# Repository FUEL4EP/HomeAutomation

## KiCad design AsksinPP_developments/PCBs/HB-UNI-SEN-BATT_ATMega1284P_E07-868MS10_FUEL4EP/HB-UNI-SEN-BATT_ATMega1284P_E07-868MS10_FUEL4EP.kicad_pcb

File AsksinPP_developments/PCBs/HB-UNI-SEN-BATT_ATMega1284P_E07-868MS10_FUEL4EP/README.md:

# HB-UNI-SEN-BATT_ATMega1284P_E07-868MS10_FUEL4EP  

**Platine für DIY AsksinPP für**
- eingebauter SMD TQFP-44 [ATMega1284P](https://ww1.microchip.com/downloads/en/DeviceDoc/doc8059.pdf) mit 128kByte Programmspeicher, 16kByte SRAM, 4kByte EEPROM
- [eByte E07-868MS10 Sendemodul](https://www.rcscomponents.kiev.ua/datasheets/e07-868ms10_usermanual_en_v1_20.pdf)
- Bestückungsoption für [Waveshare ePaper Modul (1.54inch (B)](https://www.waveshare.com/product/1.54inch-e-paper-module.htm)
- Bestückungsoption für [TPS61221 Aufwärtswandler](https://www.ti.com/lit/ds/symlink/tps61221.pdf?ts=1634546965861&ref_url=https%253A%252F%252Fwww.ti.com%252Fproduct%252FTPS61221) bei NiMH Akkumulatorbetrieb
- alle SMD Bausteine sind mit dem JLCPCB SMT Bestückungsservice kostengünstig und qualitativ hochwertig bestückbar, das ist also auch für Grobmotoriker wie mich geeignet :-)
- die Bestückungsoption ePaper wurde noch nicht validiert!

## Hinweis

- da das Funkmodul eByte E07-868MS10 (fast) nicht mehr  käuflich zu erhalten ist, wurde die Platine [HB-UNI-SEN-BATT_ATMega1284P_E07-900MM10S_FUEL4EP](https://github.com/FUEL4EP/HomeAutomation/tree/master/AsksinPP_developments/PCBs/HB-UNI-SEN-BATT_ATMega1284P_E07-900MM10S_FUEL4EP) basierend auf dem gut erhältlichen Funkmodul eByte E07-900MM10S entwickelt.

## Credits

- diese Platine ist von Alexander Reinerts Platine [HB-UNI-SEN-BATT](https://github.com/alexreinert/PCB/tree/master/HB-UNI-SEN-BATT) abgeleitet.
- vielen Dank an Alexander Reinert für die Vorarbeit.

## Platine wurde nach Fertigung bei JLCPCB erfolgreich validiert

- entwickelt mit KiCAD 6.0.11
- die Platine wurde bei JLCPCB gefertigt und mit den SMD Bauteilen bestückt
; die nicht SMD Bauteile müssen von Hand verlötet werden
- die gefertigte Platine wurde erfolgreich **ohne** Aufwärtswandler mit dem Sketch [HB-UNI-SENSOR1-AQ-BME680_KF](https://github.com/FUEL4EP/HomeAutomation/tree/master/AsksinPP_developments/sketches/HB-UNI-Sensor1-AQ-BME680_KF) validiert:

- **Update 21. Aug 2023:** Die gefertigte Platine wurde erfolgreich **mit** dem Aufwärtswandler TPS61221 validiert:

	+ die Platine wurde bei JLCPCB gefertigt und einschließlich der Induktivität mit den SMD Bauteilen bestückt 
	+ im Bild wurde ein AA-Akkumulator wurde durch eine AA-Dummy- Batterie ersetzt
	+ Betrieb ist mit einer oder zwei AA Akkumulatorbatterien möglich
	+ die Ausgangsspannung des Aufwärtswandlers beträgt 3.3 Volt
	+ der Jumper JP2 ist bei Betrieb mit einem Aufwärtswandler zu durchtrennen
	+ der Jumper JP3 ist ist bei Betrieb mit einem Aufwärtswandler mit einer Lötbrücke zu versehen

## Eigenschaften

- abgeleitet aus [HB-UNI-SEN-BATT](https://github.com/alexreinert/PCB/tree/master/HB-UNI-SEN-BATT)
- kompletter Datensatz für KiCAD 6 auf Github verfügbar:
    + 'git clone https://github.com/FUEL4EP/HomeAutomation.git' oder als [ZIP-Datei](https://github.com/FUEL4EP/HomeAutomation/archive/refs/heads/master.zip)
    + die Platinendaten sind dann unter 'HomeAutomation/AsksinPP_developments/PCBs/HB-UNI-SEN-BATT_ATMega1284P_E07-868MS10_FUEL4EP' direkt mit KiCAD aufrufbar
- neue Eigenschaften:
    + SMD Bestückung, wo möglich
    + SMD TQFP-44 [ATMega1284P](https://ww1.microchip.com/downloads/en/DeviceDoc/doc8059.pdf) mit 128kByte Programmspeicher, 16kByte SRAM, 4kByte EEPROM
    + Bestückungsoption für [Waveshare ePaper Modul (1.54inch (B)](https://www.waveshare.com/product/1.54inch-e-paper-module.htm)
    + Bestückungsoption für [TPS61221 Aufwärtswandler](https://www.ti.com/lit/ds/symlink/tps61221.pdf?ts=1634546965861&ref_url=https%253A%252F%252Fwww.ti.com%252Fproduct%252FTPS61221) bei NiMH Akkumulatorbetrieb
    + alle SMD Bausteine sind mit dem JLCPCB SMT Bestückungsservice kostengünstig und qualitativ hochwertig bestückbar, das ist also auch für Grobmotoriker wie mich gegeignet :-)
    + Stiftleiste J10 mit Versorgungsspannungen zum Gehäuseoberteil oder Akkulademodul
    + Korrektur der Abstandfehlers bei einem Batteriehalter. Beim [HB-UNI-SEN-BATT](https://github.com/alexreinert/PCB/tree/master/HB-UNI-SEN-BATT) hat das schon mal gerne zu thermischen Ausfällen durch mechanische Spannungen geführt.
    + als Funkmodul wird das [eByte E07-868MS10 Sendemodul](https://www.rcscomponents.kiev.ua/datasheets/e07-868ms10_usermanual_en_v1_20.pdf) verwendet. Dieses ist qualitativ viel besser als die üblichen grünen noname 868 MHz Funkmodule.
    + das schafft Platz für eine 8-polige Stiftleiste J11 zum optionalen Anschluss eines [Waveshare ePaper Moduls (1.54inch (B)](https://www.waveshare.com/product/1.54inch-e-paper-module.htm). Der ATMega1284P hat auch genügend RAM für die Programmierung eines 200 Pixel x 200 Pixel e-Papermoduls.
    + JLCPCB BOM and CPL Dateien für SMT Service werden [bereitgestellt](./jlcpcb/production_files)

### Benötigte Bauteile:

- bedingt durch die SMT Service von JLCPCB sind nur noch wenige Durchsteckbauteile von Hand zu verlöten:
* [eByte E07-868MS10 Sendemodul 868MHz](https://www.elecbee.com/de-24376-E07-868MS10-CC1101-Stamp-Hole-Antenna-IoT-UHF-1000m-868MHz-SPI-10dBm-Wireless-Transmitter-Transceiver-RF-Module) oder alternativ das [Elecbee CC1101 Wireless-Modul 868 MHz](https://www.elecbee.com/de-24507-CC1101-Wireless-Module-868MHz-Digital-Transmission-Receiving-Industrial-grade-RF-Communication-Transparent-Transmission) Modul
* e-Paper [Waveshare ePaper Moduls (1.54inch (B)](https://www.waveshare.com/product/1.54inch-e-paper-module.htm) (optional, Anschluss an J11)
* 2x Keystone 2460 Batteriehalter 1xAA
* Stiftleiste RM 1.27mm 1x8 Pin (für eByte E07-868MS10 Sendemodul 868MHz)
* Stiftleiste RM 2mm 1x8 Pin (für ePaper)
* Stiftleisten RM 2,54mm (nach Bedarf)
* IRLU024N (optional für Verpolungsschutz)
* Versorgung durch NiMH Akkumulatoren und Aufwärtswandler ist vorbereitet (JP2)
* Bestückungsoption Aufwärtswandler siehe [Schaltplan](Schematics/HB-UNI-SEN-BATT_ATMega1284P_E07-868MS10_FUEL4EP.pdf), unter KiCAD sind alle Referenzen eingetragen

### Aufbauhinweise

- es wird dringend angeraten, vor dem Einbau der I2C Sensoren durchzuführen
    + einen Frequenztest. Hier der Frequenztest für einen ATmega 1284p : [FreqTest_1284P.ino](../Supplements/FreqTest_1284P/FreqTest_1284P.ino)
    + einen Leckagetest. Hier der Leckagetest für einen ATmega 1284p : [SleepTest_1284P.ino](../Supplements/SleepTest_1284P/SleepTest_1284P.ino)
        + der Leckagestrom im Sleepmode sollte < 10 uA betragen

### Passende AsksinPP Projekte von FUEL4EP
   + [HB-UNI-Sensor1-AQ-BME680](https://github.com/FUEL4EP/HomeAutomation/tree/master/AsksinPP_developments/sketches/HB-UNI-Sensor1-AQ-BME680)
   + [HB-UNI-Sensor1-AQ-BME680_KF](https://github.com/FUEL4EP/HomeAutomation/tree/master/AsksinPP_developments/sketches/HB-UNI-Sensor1-AQ-BME680_KF)
   + [HB-UNI-Sensor1-AQ-BME680_KF_DEBUG](https://github.com/FUEL4EP/HomeAutomation/tree/master/AsksinPP_developments/sketches/HB-UNI-Sensor1-AQ-BME680_KF_DEBUG)
   + [HB-UNI-Sensor1-RAD-AL53](https://github.com/FUEL4EP/HomeAutomation/tree/master/AsksinPP_developments/sketches/HB-UNI-Sensor1-RAD-AL53)
   + [HB-UNI-Sensor1-THPD-SHT85](https://github.com/FUEL4EP/HomeAutomation/tree/master/AsksinPP_developments/sketches/HB-UNI-Sensor1-THPD-SHT85)
   
### Notwendige Änderung der Betriebsspannungsmessung in Sketchen
- da die Platine einen fest verdrahteten Spannungsteiler R7 und R8 für die Betriebsspannung / Akkuspannungsmessung verwendet, muss in Sketchen folgende Anpassung gegebenenfalls durchgeführt werden:

- nur notwendig, wenn die Akkuspannung / Betriebsspannung größer als 3,5 Volt ist ( 2x AA Alkaline Batterie)

- von bisher
```
// 1) Standard: tmBattery, UBatt = Betriebsspannung AVR
#define BAT_SENSOR tmBattery
```
- nach
```
// 2) für StepUp/StepDown: tmBatteryResDiv, sense pin PA0 (=pin 37), activation pin PB3 (=pin 43) , Faktor = Rges/Rlow*1000, z.B. (100kOhm+47kOhm/100kOhm), Faktor (147k)/(100k)*1000 = 1470 (ATMega1284P)
// start with Faktor = 1470
// check in serial monitor the reported V2='accumulator voltage(MCU ADC) (x1000.0)' and compare with the reported V1='accumulator batteries voltage (x1000.0)'
// calculate voltage correction factor V1/V2
// calculate total Faktor = 1470 * V2/V1 = 1470 * 3141 / 3157 = 1463
#define BAT_SENSOR tmBatteryResDiv<A0, PB3, 1463>
```
- zur Berechnung von Faktor in tmBatteryResDiv wird ein Libreoffice Calc Sheet [tmBattery_tmBatteryResDiv_calculator.ods](../../tools/tmBattery_tmBatteryResDiv_calculator.ods) zur Verfügung gestellt
- in der Version 1.0 war R8 = 200kOhm, daher Faktor = 3000 (ohne Kalibrierung)
- in der Version 1.1 ist R8 = 47kOhm, daher Faktor = 1470 (ohne Kalibrierung)

### Anschluss eines FTDI Debuggers

- zum Anschluss eines FTDI Debuggers an die 6-polige Stiftleiste J12 bitte ein [6 Pin Dupontkabel 2.54mm Buchse-Buchse 20 cm](https://www.roboter-bausatz.de/p/6-pin-dupontkabel-2.54mm-buchse-buchse-20-cm) verwenden

### Passendes Gehäuse
* Camdenboss CBRS01SWH und CBRS01VWH
* oder [Gehäuse HB-UNI-SEN-BATT snap in V2 von wpatrick](https://www.thingiverse.com/thing:3540481) für 3D-Druck
* bei Einbau eines e-Paper Moduls muss das Gehäuseoberteil angepasst werden (noch zu tun)

### Hinweise
* Achtung: Kein Überspannungsschutz vorhanden
* der Verpolungsschutz ist optional. Dafür Bauteil Q1 (IRLU024N) und R3 (100KOhm Widerstand) bestücken. Alternativ JP1 auf der Platinenrückseite brücken um ohne Verpolungsschutz zu arbeiten.
* bei der Nutzung des JLCPCB SMT Bestückungsservice ist darauf zu achten, dass **alle** benötigten SMD Bauteile als im Lager **verfügbar** angezeigt werden. Sonst bitte **NICHT** bestellen!

### KiCAD Plugin
- für die Erzeugung der JLCPCB Produktionsdaten wurde das Plugin [KiCAD JLCPCB tools](https://github.com/bouni/kicad-jlcpcb-tools) verwendet.

## Bestellen von Platinen

- die Platine kann entweder direkt bei JLCPCB bestellt werden
- die notwendigen Produktionsdaten stehen [hier](./jlcpcb/production_files/)
- oder per PN bei [FUEL4EP](https://homematic-forum.de/forum/ucp.php?i=pm&mode=compose&u=20685) im Homematic Forum nachfragen. Aus der Bestellung der Prototypen sind noch wenige Platinen kostengünstig abzugeben (Stand Juli 2023).

## passende DIY AsksinPP Funkmodule 868.3 MHz für die Fertigung bei JLCPCB
- als DIY-Ersatz für das eByte E07 868M10S Funkmodul stehen zur Verfügung:
	-  [CC1101_868MHz_RF_Modul_FUEL4EP](https://github.com/FUEL4EP/HomeAutomation/tree/master/AsksinPP_developments/PCBs/CC1101_868MHz_RF_Modul_FUEL4EP) mit Drahtantenne
	- [CC1101_868MHz_UFL_RF_Modul_FUEL4EP](https://github.com/FUEL4EP/HomeAutomation/tree/master/AsksinPP_developments/PCBs/CC1101_868MHz_UFL_RF_Modul_FUEL4EP) mit U.FL Antennenbuchse
- alternativ für das Funkmodul eByte E07 868M10S kann der Adapter [Adapter_EByte_E07_900MM10S_to_Ebyte_E07_868MS10_FUEL4EP](https://github.com/FUEL4EP/HomeAutomation/tree/master/AsksinPP_developments/PCBs/Adapter_EByte_E07_900MM10S_to_Ebyte_E07_868MS10_FUEL4EP) bestückt mit einem Funkmodul eByte E07 900MM10S verwendet werden
	
## passende DIY I2C-Sensormodule für die Fertigung bei JLCPCB
- als DIY-Ersatz für kommerzielle Sensormodule stehen folgende passende Adapterplatinen zur Verfügung:
	- [I2C_Module_BME280_FUEL4EP](https://github.com/FUEL4EP/HomeAutomation/tree/master/AsksinPP_developments/PCBs/I2C_Module_BME280_FUEL4EP)
	- [I2C_Module_BME680_FUEL4EP](https://github.com/FUEL4EP/HomeAutomation/tree/master/AsksinPP_developments/PCBs/I2C_Module_BME680_FUEL4EP)
	- [I2C_Module_SHT85_BME280_FUEL4EP](https://github.com/FUEL4EP/HomeAutomation/tree/master/AsksinPP_developments/PCBs/I2C_Module_SHT85_BME280_FUEL4EP)
	- [I2C_Module_SHT45_BME280_FUEL4EP](https://github.com/FUEL4EP/HomeAutomation/tree/master/AsksinPP_developments/PCBs/I2C_Module_SHT45_BME280_FUEL4EP)
	- [4Bit_I2C_Port_Expander_Module_FUEL4EP](https://github.com/FUEL4EP/HomeAutomation/tree/master/AsksinPP_developments/PCBs/4Bit_I2C_Port_Expander_Module_FUEL4EP)

## Disclaimer

-   die Nutzung der hier veröffentlichten Inhalte erfolgt vollständig auf eigenes Risiko und ohne jede Gewähr.

## Versionsverlauf

-    V1.1 10. Jan 2022: R8 auf 47 kOhm geändert, zusätzliche Aufdrucktexte
-    V1.2 15. Jul 2023: Migration der Datenbasen zu KiCAD 6, als Induktivität    	                     für den Aufwärtswandler wird nun LQH3NPN4R7MM0L von
                         Murata Electronics verwendet, die bei JLCPCB bestellbar ist  (eventuell ist eine Vorbestellung notwendig)
-	 V1.3 24. Jul 2023:	KiCAD 6 bedingte Verbesserungen der Datenbasis
-	 V1.4 15. Aug 2023:	Fix of En pin of TPS61221 boost converter (must be tied to VIN)
     S V1.3 17. Feb 2024 Fix der falschen LCSC-Nummer von R7 / Layout bleibt unverändert
     V1.5   26. Sep 2024 Migration der Datenbasen zu KiCAD 8, Fix von LCSC-Nummern (R2, R4, R5 , Fixes für KiCAD 8

- 	KiCad Schaltplan-Editor   Version: 8.0.5-8.0.5-0~ubuntu22.04.1, release build
 unter Kubuntu22.04.1
- 	KiCad Leiterplatteneditor Version: 8.0.5-8.0.5-0~ubuntu22.04.1, release build
 unter Kubuntu22.04.1
- 	PCB Version 1.5
- 	Schematics  1.5

## Lizenz 

**Creative Commons BY-NC-SA**<br>
Give Credit, NonCommercial, ShareAlike

<br />This work is licensed under a <a rel="license" href="http://creativecommons.org/licenses/by-nc-sa/4.0/">Creative Commons Attribution-NonCommercial-ShareAlike 4.0 International License</a>.

-EOF

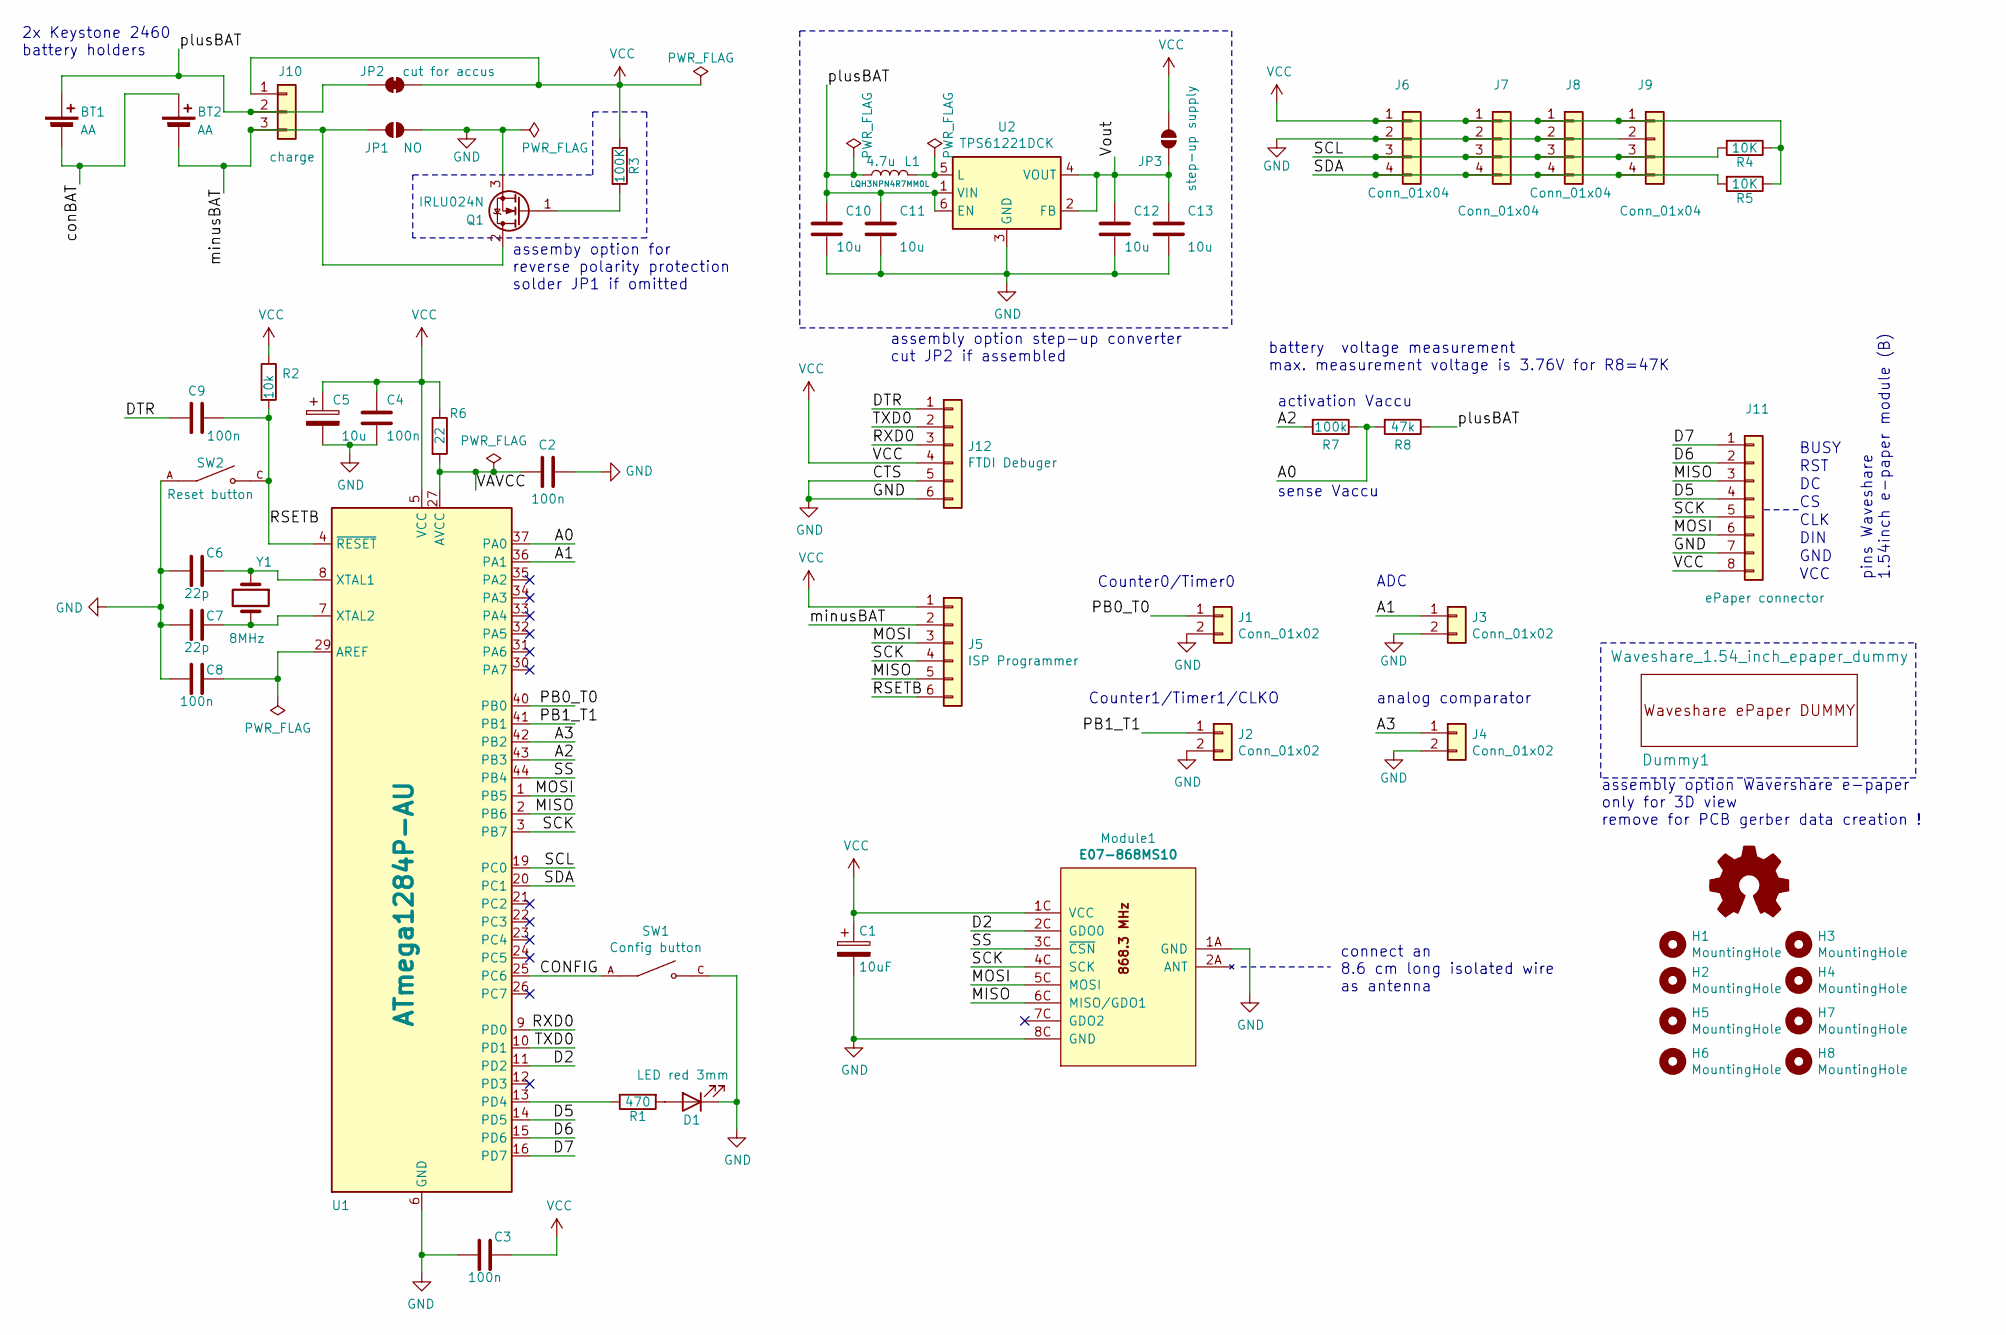
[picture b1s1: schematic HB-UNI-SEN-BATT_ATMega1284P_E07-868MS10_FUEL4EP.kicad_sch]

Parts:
BT1, BT2: AA; BatteryHolder_Keystone_2460_1xAA
C1: 10uF; C_1206_3216Metric_Pad1.33x1.80mm_HandSolder; LCSC C7171
C2, C3, C4, C8, C9: 100n; C_0805_2012Metric; LCSC C28233
C5: 10u; C_1206_3216Metric_Pad1.33x1.80mm_HandSolder; LCSC C7171
C6, C7: 22p; C_0805_2012Metric; LCSC C1804
C10, C11, C12, C13: 10u; C_0805_2012Metric; LCSC C15850
D1: LED red 3mm; LED_0805_2012Metric_Pad1.15x1.40mm_HandSolder; LCSC C84256
Dummy1: Waveshare_1.54_inch_epaper_dummy; Waveshare_ePaper_module
H1, H2, H3, H4: MountingHole; MountingHole_2.2mm_M2_Pad_Via
H5, H6, H7, H8: MountingHole; ePaper_MountingHole_M5
J1, J2, J3, J4: Conn_01x02; PinHeader_1x02_P2.54mm_Vertical
J5: ISP Programmer; PinHeader_1x06_P2.54mm_Vertical
J6, J7, J8, J9: Conn_01x04; PinHeader_1x04_P2.54mm_Vertical
J10: charge; PinHeader_1x03_P2.54mm_Vertical
J11: ePaper connector; PinPads_1x08_P2.00mm_Vertical
J12: FTDI Debuger; PinHeader_1x06_P2.54mm_Vertical
JP1: NO; SolderJumper-2_P1.3mm_Open_Pad1.0x1.5mm
JP2: cut for accus; SolderJumper-2_P1.3mm_Bridged_Pad1.0x1.5mm
JP3: step-up supply; SolderJumper-2_P1.3mm_Open_Pad1.0x1.5mm
L1: 4.7u; FUEL4EP_Inductor_SMD_1; LCSC C86077
LOGO1: Logo_Open_Hardware_Small; CC-BY-ND-SA
Module1: E07-868MS10; eByte_E07-868MS10
Q1: IRLU024N; TO-251-3_Vertical; LCSC C558184
R1: 470; R_0805_2012Metric_Pad1.20x1.40mm_HandSolder; LCSC C17710
R2: 10k; R_0805_2012Metric_Pad1.20x1.40mm_HandSolder; LCSC C17414
R3: 100K; R_0805_2012Metric_Pad1.20x1.40mm_HandSolder; LCSC C340475
R4, R5: 10K; R_0805_2012Metric_Pad1.20x1.40mm_HandSolder; LCSC C17414
R6: 22; R_0805_2012Metric_Pad1.20x1.40mm_HandSolder; LCSC C23345
R7: 100k; R_0805_2012Metric_Pad1.20x1.40mm_HandSolder; LCSC C149504
R8: 47k; R_0805_2012Metric_Pad1.20x1.40mm_HandSolder; LCSC C17713
SW1: Config button; SW_TS-1187A-B-A-B; PARTREV A0; LCSC C318884
SW2: Reset button; SW_TS-1187A-B-A-B; PARTREV A0; LCSC C318884
U1: ATmega1284P-AU; TQFP-44_10x10mm_P0.8mm; LCSC C33575
U2: TPS61221DCK; Texas_R-PDSO-G6; LCSC C2865756
Y1: 8MHz; Crystal_SMD_5032-2Pin_5.0x3.2mm_HandSoldering; LCSC C115962

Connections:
/A0: R7.1, R8.2, U1.37 (PA0)
/A1: J3.1, U1.36 (PA1)
/A2: R7.2, U1.43 (PB3)
/A3: J4.1, U1.42 (PB2)
/CONFIG: SW1.A, SW1.B (e), U1.25 (PC6)
/D2: Module1.2C (GDO0), U1.11 (PD2)
/D5: J11.4, U1.14 (PD5)
/D6: J11.2, U1.15 (PD6)
/D7: J11.1, U1.16 (PD7)
/DTR: C9.2, J12.1
/MISO: J5.5, J11.3, Module1.6C (MISO/GDO1), U1.2 (PB6)
/MOSI: J5.3, J11.6, Module1.5C (MOSI), U1.1 (PB5)
/PB0_T0: J1.1, U1.40 (PB0)
/PB1_T1: J2.1, U1.41 (PB1)
/RSETB: C9.1, J5.6, R2.2, SW2.C, SW2.D, U1.4 (~RESET)
/RXD0: J12.3, U1.9 (PD0)
/SCK: J5.4, J11.5, Module1.4C (SCK), U1.3 (PB7)
/SCL: J6.3, J7.3, J8.3, J9.3, R4.2, U1.19 (PC0)
/SDA: J6.4, J7.4, J8.4, J9.4, R5.2, U1.20 (PC1)
/SS: Module1.3C (~CSN), U1.44 (PB4)
/TXD0: J12.2, U1.10 (PD1)
/VAVCC: C2.2, R6.2, U1.27 (AVCC)
/Vout: C12.1, C13.1, JP3.1 (A), U2.2 (FB), U2.4 (VOUT)
/conBAT: BT1.2 (-), BT2.1 (+)
/minusBAT: BT2.2 (-), J5.2, J10.3, JP1.1 (A), Q1.2 (D)
/plusBAT: BT1.1 (+), C10.1, C11.1, J10.2, JP2.1 (A), L1.1, R8.1, U2.1 (VIN), U2.6 (EN)
GND: C1.2, C2.1, C3.2, C4.2, C5.2, C6.2, C7.2, C8.2, C10.2, C11.2, C12.2, C13.2, D1.1 (K), J1.2, J2.2, J3.2, J4.2, J6.2, J7.2, J8.2, J9.2, J11.7, J12.5, J12.6, JP1.2 (B), Module1.1A (GND), Module1.8C (GND), Q1.3 (S), SW1.C, SW1.D, SW2.A, SW2.B (e), U1.6 (GND), U1.18 (GND), U1.28 (GND), U1.39 (GND), U2.3 (GND)
unnamed: D1.2 (A), R1.2
unnamed: Q1.1 (G), R3.2
unnamed: C8.1, U1.29 (AREF)
unnamed: R1.1, U1.13 (PD4)
unnamed: C6.1, U1.8 (XTAL1), Y1.1
unnamed: C7.1, U1.7 (XTAL2), Y1.2
unnamed: L1.2, U2.5 (L)
VCC: C1.1, C3.1, C4.1, C5.1, J5.1, J6.1, J7.1, J8.1, J9.1, J10.1, J11.8, J12.4, JP2.2 (B), JP3.2 (B), Module1.1C (VCC), R2.1, R3.1, R4.1, R5.1, R6.1, U1.5 (VCC), U1.17 (VCC), U1.38 (VCC)

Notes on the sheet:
RST
CLK
analog comparator
connect an 8.6 cm long isolated wire as antenna
VCC
activation Vaccu
Counter1/Timer1/CLKO
assemby option for reverse polarity protection solder JP1 if omitted
Counter0/Timer0
ADC
assembly option step-up converter cut JP2 if assembled
battery voltage measurement max. measurement voltage is 3.76V for R8=47K
pins Waveshare 1.54inch e-paper module (B)
sense Vaccu
2x Keystone 2460 battery holders
GND
DIN
BUSY
assembly option Wavershare e-paper only for 3D view remove for PCB gerber data creation !

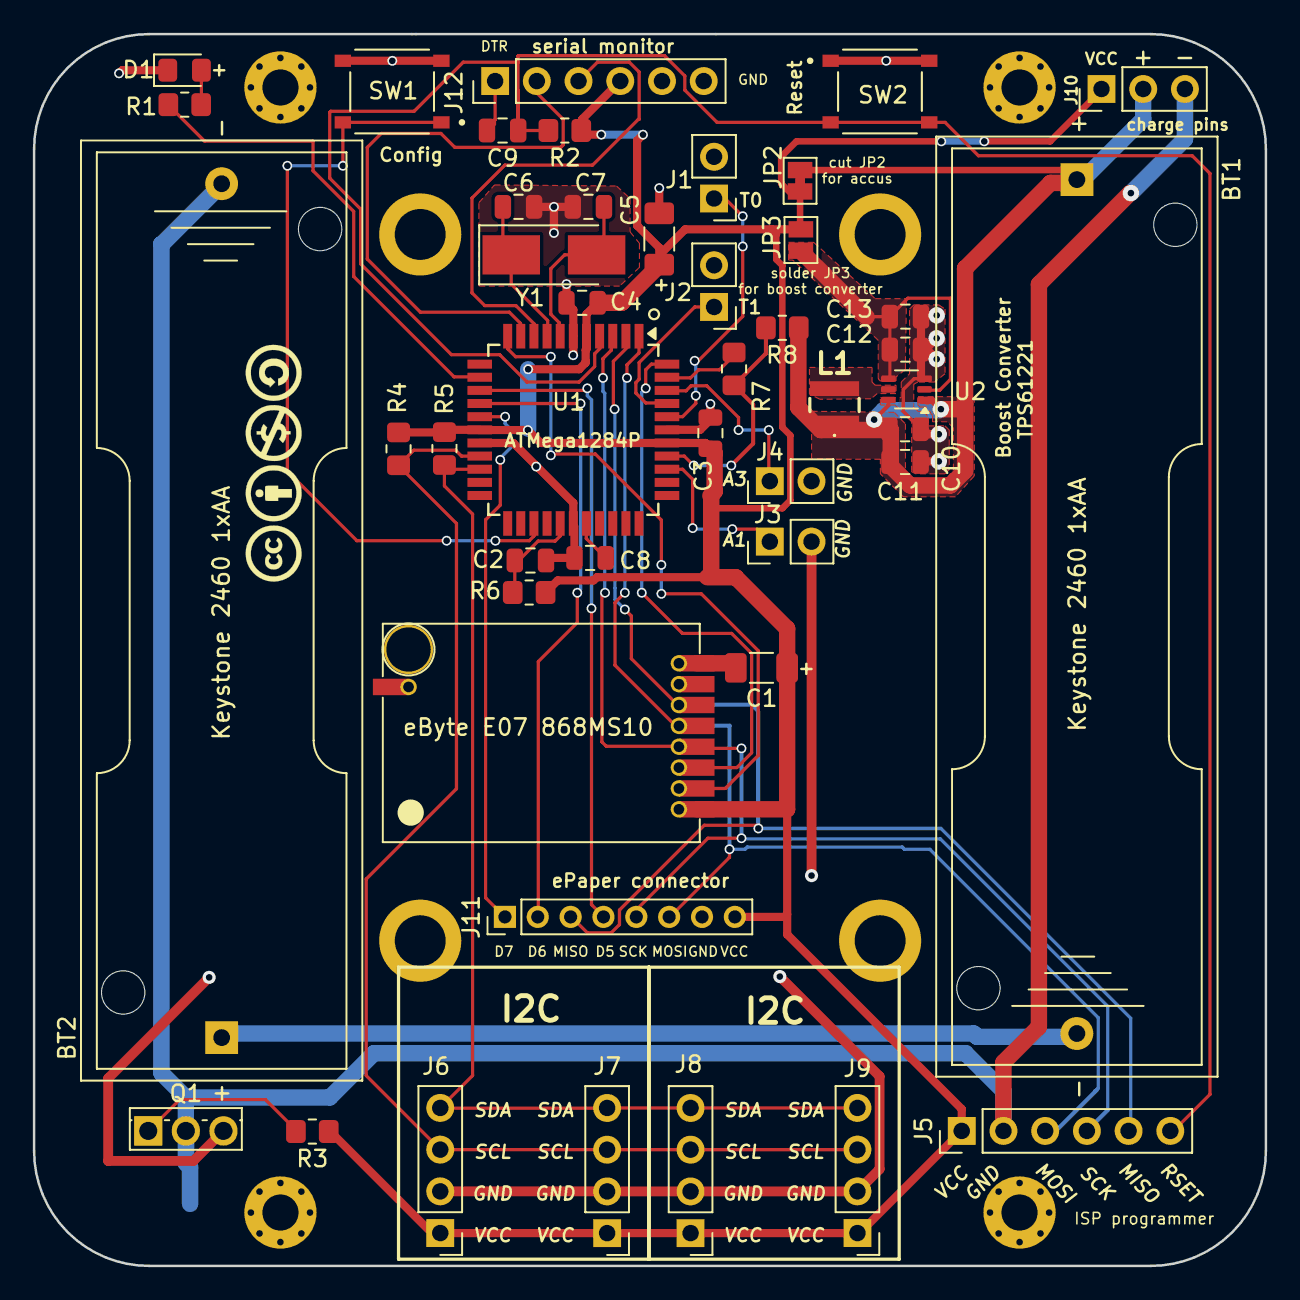
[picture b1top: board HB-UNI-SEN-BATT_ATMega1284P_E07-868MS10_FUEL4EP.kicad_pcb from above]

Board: 2 copper layers, 75.0 x 75.0 mm, 56 parts (0 on the bottom side), 35 nets.

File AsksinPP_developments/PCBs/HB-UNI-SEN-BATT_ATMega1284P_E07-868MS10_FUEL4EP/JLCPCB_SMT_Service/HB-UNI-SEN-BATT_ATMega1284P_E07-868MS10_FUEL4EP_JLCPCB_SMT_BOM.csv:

"Comment","Designator","Footprint","LCSC Part Number"
"10uF Polarized capacitor","C1","=""CASE-A_3216""","C7171"
"100n Unpolarized capacitor","C2,C3,C4,C8,C9","=""0805""","C28233"
"10u Polarized capacitor","C5","=""CASE-A_3216""","C7171"
"22p Unpolarized capacitor","C6,C7","=""0805""","C1804"
"10u Unpolarized capacitor","C10,C11,C12,C13","=""0805""","C15850"
"LED red 3mm Light emitting diode","D1","=""LED_0805""","C84256"
"IRLU024N N-MOSFET transistor, gate/drain/source","Q1","=""TO-251""","C558184"
"470 Resistor","R1","=""0805""","C17710"
"10k Resistor","R2","=""0805""","C17733"
"100K Resistor","R3","=""R0805""","C101406"
"10K Resistor","R4,R5","=""R0805""","C101405"
"22 Resistor","R6","=""0603""","C23345"
"100k Resistor","R7","=""0805""","C25271"
"47k Resistor","R8","=""0805""","C17713"
"Config button SMD Push Button Switch JLCPCB Basic","SW1","=""SMD-SW-4_5.1x5.1x1.5""","C318884"
"Reset button SMD Push Button Switch JLCPCB Basic","SW2","=""SMD-SW-4_5.1x5.1x1.5""","C318884"
"ATmega1284P-AU 20MHz, 128kB Flash, 16kB SRAM, 4kB EEPROM, JTAG, TQFP-44","U1","=""TQFP-44_10.0x10.0x0.8P""","C33575"
"TPS61221DCK 400 mA Step-Up Converter, Fixed 3.3V Output Voltage, 0.7-5.5V Input Voltage, SC-70","U2","=""SOT-363""","C37055"
"8MHz Two pin crystal","Y1","=""SMD-5032_2P""","C115962"

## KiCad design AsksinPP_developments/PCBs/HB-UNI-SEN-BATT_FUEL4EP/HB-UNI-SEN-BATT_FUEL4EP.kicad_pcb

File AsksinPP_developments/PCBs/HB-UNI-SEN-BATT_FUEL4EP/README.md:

# HB-UNI-SEN-BATT_FUEL4EP  

**Platine für DIY AsksinPP Projekte basierend auf den folgenden möglichen Arduino-Modulen:**
- [Arduino Pro Mini 328 - 3.3V/8MHz](https://www.sparkfun.com/arduino-pro-mini-328-3-3v-8mhz.html): 32kByte Programmspeicher, 4kByte SRAM, 1kByte EEPROM
- NEU: [HB_Pro_Mini_ATMEGA1284P_FUEL4EP](https://github.com/FUEL4EP/HomeAutomation/tree/master/AsksinPP_developments/PCBs/HB_Pro_Mini_ATMEGA1284P_FUEL4EP)
	+ mit deutlich mehr Programm-, RAM- und EEPROM-Speicher als Arduino Pro Mini: 128kByte Programmspeicher, 16kByte SRAM, 4kByte EEPROM)
- [Tindie Pro Mini XL - v2 - ATmega 1284p](https://www.tindie.com/products/prominimicros/pro-mini-xl-v2-atmega-1284p/)
	+ mit deutlich mehr Programm-, RAM- und EEPROM-Speicher als Arduino Pro Mini: 128kByte Programmspeicher, 16kByte SRAM, 4kByte EEPROM)

## Credits

- diese Platine ist von Alexander Reinerts Platine [HB-UNI-SEN-BATT](https://github.com/alexreinert/PCB/tree/master/HB-UNI-SEN-BATT) abgeleitet.
- vielen Dank an Alexander Reinert für die Vorarbeit.

## Status der Validierung der Platine

- Platine wurde bis zur Version V1.4 bei JLCPCB erfolgreich gefertigt und validiert
- auch der Prototyp der neuen Platinenversion V1.5 wurde bei JLCPCB gefertigt und danach erfolgreich validiert:

- für die Systemvalidierung wude als Hardware verwandt:
	+ [HB-UNI-SEN-BATT_FUEL4EP V1.5](https://github.com/FUEL4EP/HomeAutomation/tree/master/AsksinPP_developments/PCBs/HB-UNI-SEN-BATT_FUEL4EP)
	+ [HB_Pro_Mini_ATMEGA1284P_FUEL4EP V1.0](https://github.com/FUEL4EP/HomeAutomation/tree/master/AsksinPP_developments/PCBs/HB_Pro_Mini_ATMEGA1284P_FUEL4EP)
	+ [I2C_Module_SHT45_BME280_small_FUEL4EP V1.5](https://github.com/FUEL4EP/HomeAutomation/tree/master/AsksinPP_developments/PCBs/I2C_Module_SHT45_BME280_small_FUEL4EP)
	+ getestet wurden folgende Spannungsversorgungen:
		* 1x AA Alkaline Batterie
		* 2x AA Alkaline Batterie
		* 1x NiMH AA Akkumulator
		* 2x NiMH AA Akkumulator
- für die Systemvalidierung wurde als Software verwendet:
	+ [HB-UNI-Sensor1-THPD-SHT45_BME280](https://github.com/FUEL4EP/HomeAutomation/tree/master/AsksinPP_developments/sketches/HB-UNI-Sensor1-THPD-SHT45_BME280)
	+ die Stromaufnahme im Schlafmodus mit 1x AA Alkaline Battterie beträgt ca. 22uA.

## Eigenschaften

- Weiterentwicklung von [HB-UNI-SEN-BATT](https://github.com/alexreinert/PCB/tree/master/HB-UNI-SEN-BATT) mit denselben Außenmaßen
- neue Eigenschaften:
	+ alternativ werden verschiedene Arduino Module unterstützt:
		- [Arduino Pro Mini 328 - 3.3V/8MHz](https://www.sparkfun.com/arduino-pro-mini-328-3-3v-8mhz.html): 32kByte Programmspeicher, 4kByte SRAM, 1kByte EEPROM
		- [HB_Pro_Mini_ATMEGA1284P_FUEL4EP](https://github.com/FUEL4EP/HomeAutomation/tree/master/AsksinPP_developments/PCBs/HB_Pro_Mini_ATMEGA1284P_FUEL4EP)
			+ mit deutlich mehr Programm-, RAM- und EEPROM-Speicher als Arduino Pro Mini: 128kByte Programmspeicher, 16kByte SRAM, 4kByte EEPROM)
			+ mit optionalem Boost-Konverter für Betrieb mit NiMH-Akkumulatoren oder nur einer AA Alkaline Battterie
		- [Tindie Pro Mini XL - v2 - ATmega 1284p](https://www.tindie.com/products/prominimicros/pro-mini-xl-v2-atmega-1284p/)
			+ mit deutlich mehr Programm-, RAM- und EEPROM-Speicher als Arduino Pro Mini: 128kByte Programmspeicher, 16kByte SRAM, 4kByte EEPROM

    + nur eine LED
    + dafür optionale Unterstützung von Akkumulatorbetrieb mit einem externen 'Huckepack' Aufwärtswandlermodul (siehe z.B. [HB-UNI-SENSOR1-CO2-SCD30](https://github.com/FUEL4EP/HomeAutomation/tree/master/AsksinPP_developments/sketches/HB-UNI-Sensor1-CO2_SCD30)
    + Stiftleiste J10 mit Versorgungsspannungen zum Gehäuseoberteil oder Akkulademodul
    + Korrektur der Abstandfehlers bei einem Batteriehalter. Beim [HB-UNI-SEN-BATT](https://github.com/alexreinert/PCB/tree/master/HB-UNI-SEN-BATT) hat das schon mal gerne zu thermischen Ausfällen durch mechanische Spannungen geführt.

### Benötigte Bauteile:
* eines der folgenden Arduino Module
	- [Arduino Pro Mini 328 - 3.3V/8MHz](https://www.sparkfun.com/arduino-pro-mini-328-3-3v-8mhz.html)
	- [HB_Pro_Mini_ATMEGA1284P_FUEL4EP](https://github.com/FUEL4EP/HomeAutomation/tree/master/AsksinPP_developments/PCBs/HB_Pro_Mini_ATMEGA1284P_FUEL4EP)
	- [Tindie Pro Mini XL - v2 - ATmega 1284p](https://www.tindie.com/products/prominimicros/pro-mini-xl-v2-atmega-1284p/)
* CC1101 Modulplatine 868MHz
* 1x LEDs 3mm Low Current (Pin 4)
* 1x 470Ohm Widerstände (Vorwiderstand für LED)
* Elko 10uF 1,5mm
* 2x Keystone 2460 Batteriehalter 1xAA (oder Goobay 1xAA Batteriehalter)
* Mikroschalter 6*6mm
* Stiftleiste RM 2mm 1x8 Pin (für CC1101)
* Stiftleisten RM 2,54mm (nach Bedarf)
* IRLU024N (optional für Verpolungsschutz)
* 100KOhm Widerstand (optional für Verpolungsschutz)
* 2x 10KOhm Widerstand (Pullup für I2C)
* Versorgung durch NiMH Akkumulatoren und Aufwärtswandler ist vorbereitet (JP2)

### Aufbauhinweise

- es wird dringend angeraten, vor dem Einbau der I2C Sensoren durchzuführen
    + einen Frequenztest. Hier der Frequenztest für einen [Tindie Pro Mini XL - v2 - ATmega 1284p](https://www.tindie.com/products/prominimicros/pro-mini-xl-v2-atmega-1284p/) : [FreqTest_1284P.ino](../Supplements/FreqTest_1284P/FreqTest_1284P.ino)
    + einen Leckstromtest. Hier der Leckstromtest für einen [Tindie Pro Mini XL - v2 - ATmega 1284p](https://www.tindie.com/products/prominimicros/pro-mini-xl-v2-atmega-1284p/) : [SleepTest_1284P.ino](../Supplements/SleepTest_1284P/SleepTest_1284P.ino)
        + der Leckstrom im Sleepmode sollte < 10 uA betragen
    + für einen Arduino Pro Mini die entsprechenden Standardsketche für den Frequenztest und den SleepTest verwenden.
    + am besten diese beiden Tests in einem Testaufbau mit Stecksockeln vor dem Einlöten durchführen

## Konfiguration der Überbrückungen

- bitte die Platinenüberbrückungen vor Inbetriebnahme je nach gewählter Hardwarekonfiguration wählen:

- die Tabellen dazu sind [hier](./Jumper_settings) zu finden
    
## lokale Installation des Github Releases auf Deinem Computer

- gehe bitte in Dein Zielinstallationsverzeichnis, wo Du mit der HB-UNI-SEN-BATT_FUEL4EP Platine mit KiCAD arbeiten möchtest

  - gebe dort 'git clone https://github.com/FUEL4EP/HomeAutomation.git' ein
	  + damit lädst Du mein [Sammelrepository](https://github.com/FUEL4EP/HomeAutomation) für alle meine auf Github freigegebenen HomeBrew Entwicklungen herunter.
  - dann findest Du ein neues Verzeichnis 'HomeAutomation' auf Deinem Rechner, das alle meine auf Github freigebenen Entwicklungen enthält, siehe [README.md](https://github.com/FUEL4EP/HomeAutomation/blob/master/README.md)
  	+ mache bitte regelmäßig ein Update mit 'git pull'
 -	die Platine HB-UNI-SEN-BATT_FUEL4EP findest Du unter './HomeAutomation/tree/master/AsksinPP_developments/PCBs/HB-UNI-SEN-BATT_FUEL4EP'
 
- alternativ kann vom Github [Sammelrepository](https://github.com/FUEL4EP/HomeAutomation) die ZIP-Datei HomeAutomation-master.zip heruntergeladen und auf dem lokalen Rechner ausgepackt werden. Bitte dann regelmäßig auf Github nach Updates schauen.

### Passende AsksinPP Projekte von FUEL4EP
- Arduino Pro Mini ATMega328P oder Tindie Pro Mini XL - v2 - ATmega 1284p basierend:
    + [HB-UNI-Sensor1-THPD-BME280](https://github.com/FUEL4EP/HomeAutomation/tree/master/AsksinPP_developments/sketches/HB-UNI-Sensor1-THPD-BME280)
    + [HB-UNI-Sensor1-TH-SHT75](https://github.com/FUEL4EP/HomeAutomation/tree/master/AsksinPP_developments/sketches/HB-UNI-Sensor1-TH-SHT75)
     + [HB-UNI-Sensor1-CO2_SCD30](https://github.com/FUEL4EP/HomeAutomation/tree/master/AsksinPP_developments/sketches/HB-UNI-Sensor1-CO2_SCD30)
- [HB_Pro_Mini_ATMEGA1284P_FUEL4EP](https://github.com/FUEL4EP/HomeAutomation/tree/master/AsksinPP_developments/PCBs/HB_Pro_Mini_ATMEGA1284P_FUEL4EP) oder [Tindie Pro Mini XL - v2 - ATmega 1284p](https://www.tindie.com/products/prominimicros/pro-mini-xl-v2-atmega-1284p/) basierend:
     + [HB-UNI-Sensor1-AQ-BME680](https://github.com/FUEL4EP/HomeAutomation/tree/master/AsksinPP_developments/sketches/HB-UNI-Sensor1-AQ-BME680)
    + [HB-UNI-Sensor1-AQ-BME680_KF](https://github.com/FUEL4EP/HomeAutomation/tree/master/AsksinPP_developments/sketches/HB-UNI-Sensor1-AQ-BME680_KF)
    + [HB-UNI-Sensor1-AQ-BME680_KF_DEBUG](https://github.com/FUEL4EP/HomeAutomation/tree/master/AsksinPP_developments/sketches/HB-UNI-Sensor1-AQ-BME680_KF_DEBUG)
    + [HB-UNI-Sensor1-RAD-AL53](https://github.com/FUEL4EP/HomeAutomation/tree/master/AsksinPP_developments/sketches/HB-UNI-Sensor1-RAD-AL53)
    + [HB-UNI-Sensor1-THPD-SHT85](https://github.com/FUEL4EP/HomeAutomation/tree/master/AsksinPP_developments/sketches/HB-UNI-Sensor1-THPD-SHT85)

### Passendes Gehäuse
* Camdenboss CBRS01SWH und CBRS01VWH
* oder [Gehäuse HB-UNI-SEN-BATT snap in V2 von wpatrick](https://www.thingiverse.com/thing:3540481) für 3D-Druck

### Hinweise
* Achtung: Kein Überspannungschutz vorhanden
* der Verpolungsschutz ist optional. Dafür Bauteil Q1 (IRLU024N) und R3 (100KOhm Widerstand) bestücken. Alternativ JP1 auf der Platinenrückseite überbrücken, um ohne Verpolungsschutz zu arbeiten.

### KiCAD Plugin
- für die Erzeugung der JLCPCB Produktionsdaten wurde das Plugin [KiCAD JLCPCB tools](https://github.com/bouni/kicad-jlcpcb-tools) verwendet.

## Bestellen von Platinen

- die Platine kann entweder direkt bei JLCPCB bestellt werden
- die notwendigen Produktionsdaten stehen [hier](./jlcpcb/production_files/)
- oder per PN bei [FUEL4EP](https://homematic-forum.de/forum/ucp.php?i=pm&mode=compose&u=20685) im Homematic Forum nachfragen. Aus der Bestellung der Prototypen sind noch Platinen kostengünstig abzugeben (Stand 13. Juli 2023).
	
## passende DIY I2C-Sensormodule für die Fertigung bei JLCPCB
- als DIY-Ersatz für kommerzielle Sensormodule stehen folgende passende Adapterplatinen zur Verfügung:
	- [I2C_Module_BME280_FUEL4EP](https://github.com/FUEL4EP/HomeAutomation/tree/master/AsksinPP_developments/PCBs/I2C_Module_BME280_FUEL4EP)
	- [I2C_Module_BME680_FUEL4EP](https://github.com/FUEL4EP/HomeAutomation/tree/master/AsksinPP_developments/PCBs/I2C_Module_BME680_FUEL4EP)
	- [I2C_Module_SHT85_BME280_FUEL4EP](https://github.com/FUEL4EP/HomeAutomation/tree/master/AsksinPP_developments/PCBs/I2C_Module_SHT85_BME280_FUEL4EP)
	- [I2C_Module_SHT45_BME280_FUEL4EP](https://github.com/FUEL4EP/HomeAutomation/tree/master/AsksinPP_developments/PCBs/I2C_Module_SHT45_BME280_FUEL4EP)
	- [4Bit_I2C_Port_Expander_Module_FUEL4EP](https://github.com/FUEL4EP/HomeAutomation/tree/master/AsksinPP_developments/PCBs/4Bit_I2C_Port_Expander_Module_FUEL4EP)

## Versionen
- KiCad Schaltplan-Editor Version: 8.0.9-8.0.9-0~ubuntu22.04.1, release build unter Kubuntu22.04.1
- KiCad Leiterplatteneditor Version: 8.0.9-8.0.9-0~ubuntu22.04.1, release build unter Kubuntu22.04.1 1.
- aktuelle PCB Version 1.5 
- aktuelle Schematics Version 1.3 

## Disclaimer

-  die Nutzung der hier veröffentlichten Inhalte erfolgt vollständig auf eigenes Risiko und ohne jede Gewähr.

## Lizenz 

**Creative Commons BY-NC-SA**<br>
Give Credit, NonCommercial, ShareAlike

<br />This work is licensed under a <a rel="license" href="http://creativecommons.org/licenses/by-nc-sa/4.0/">Creative Commons Attribution-NonCommercial-ShareAlike 4.0 International License</a>.

-EOF

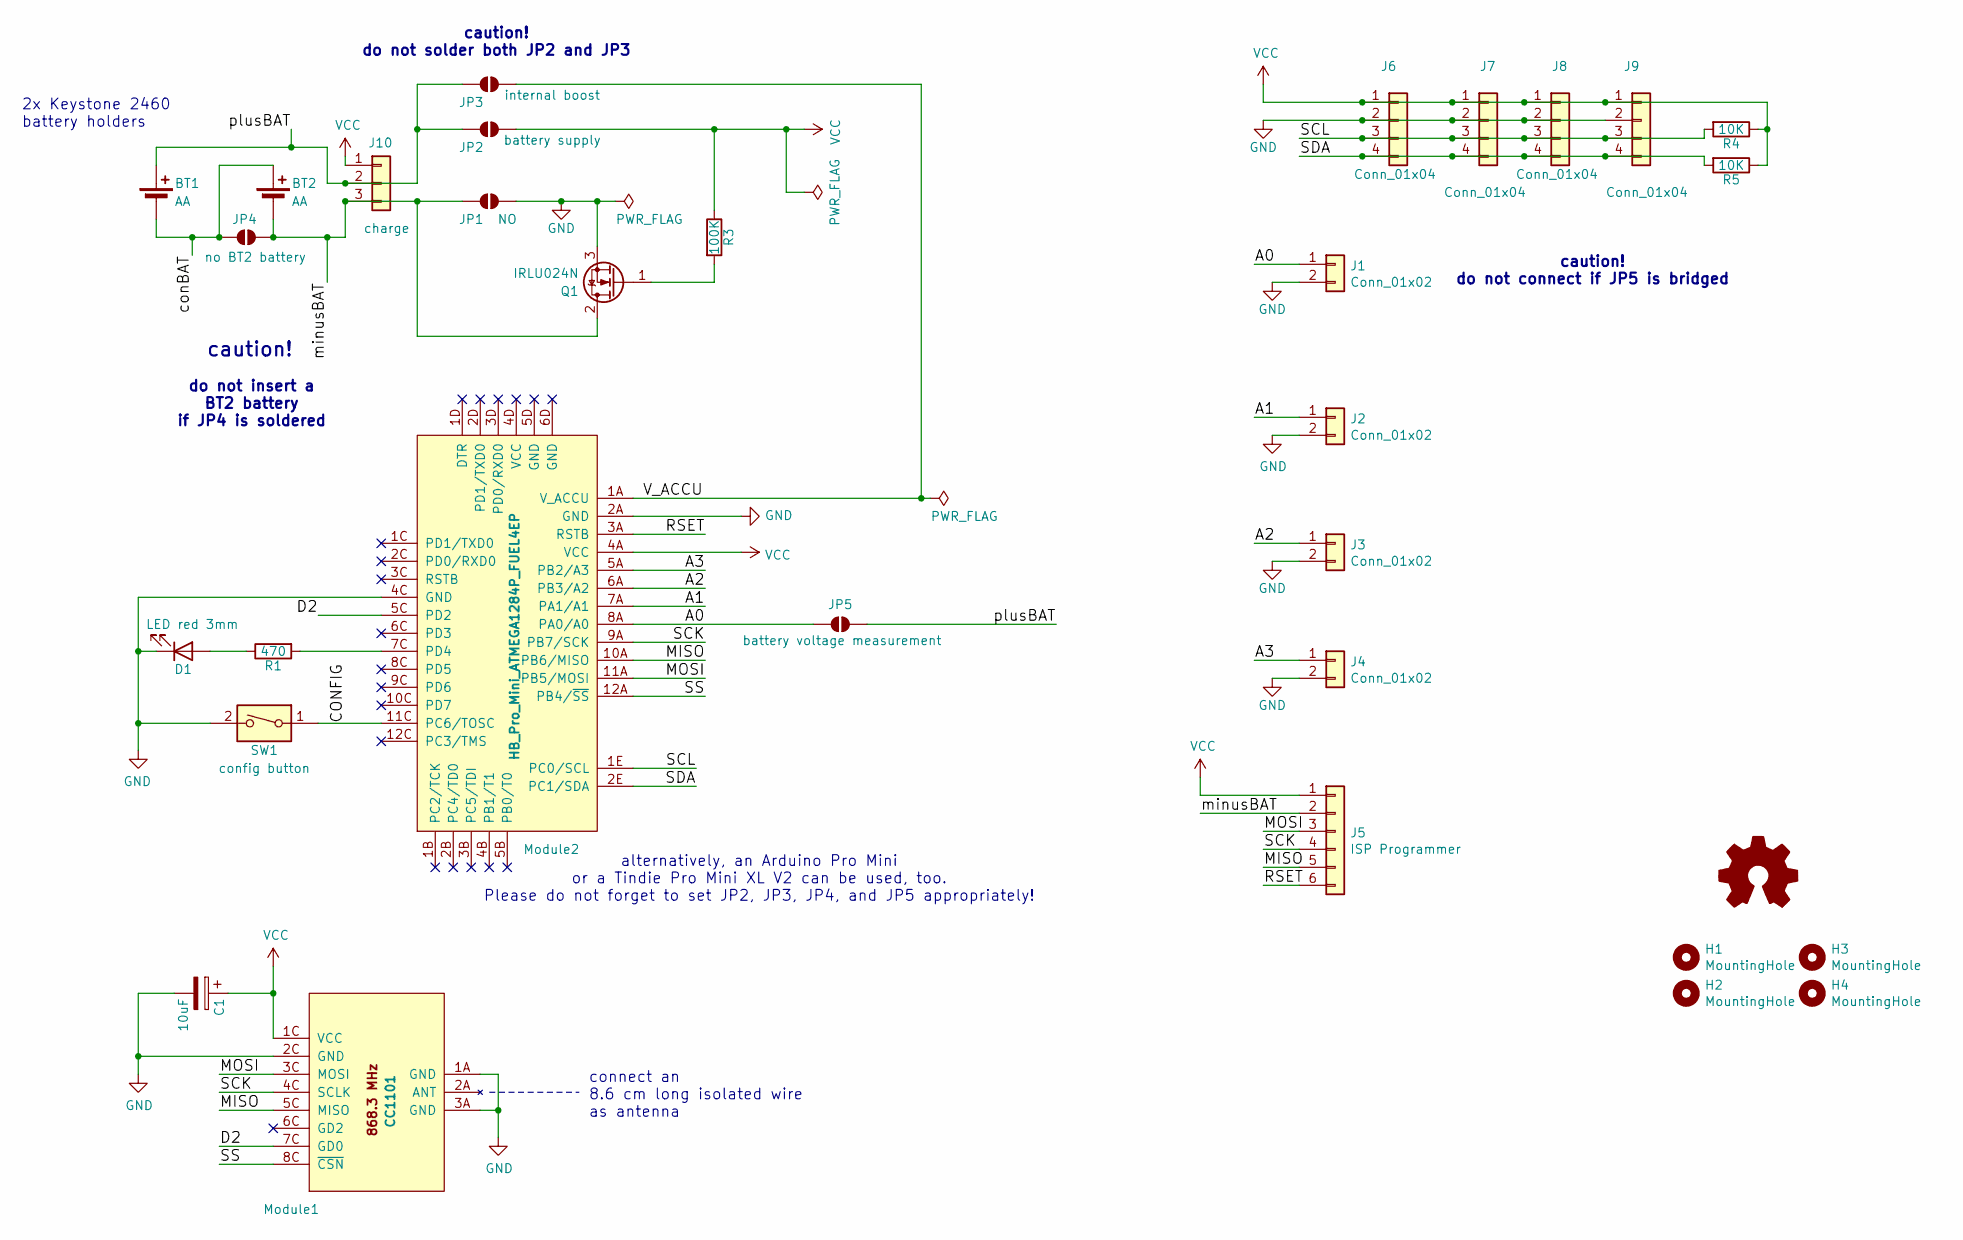
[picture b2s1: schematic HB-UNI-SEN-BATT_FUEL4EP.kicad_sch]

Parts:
BT1, BT2: AA; BatteryHolder_Keystone_2460_1xAA
C1: 10uF; CP_Radial_D4.0mm_P1.50mm
D1: LED red 3mm; LED_D3.0mm
H1, H2, H3, H4: MountingHole; MountingHole_2.2mm_M2_Pad_Via
J1, J2, J3, J4: Conn_01x02; PinHeader_1x02_P2.54mm_Vertical
J5: ISP Programmer; PinHeader_1x06_P2.54mm_Vertical
J6, J7, J8, J9: Conn_01x04; PinHeader_1x04_P2.54mm_Vertical
J10: charge; PinHeader_1x03_P2.54mm_Vertical
JP1: NO; SolderJumper-2_P1.3mm_Open_Pad1.0x1.5mm
JP2: battery supply; SolderJumper-2_P1.3mm_Open_Pad1.0x1.5mm
JP3: internal boost; SolderJumper-2_P1.3mm_Open_Pad1.0x1.5mm
JP4: no BT2 battery; SolderJumper-2_P1.3mm_Open_Pad1.0x1.5mm
JP5: battery voltage measurement; SolderJumper-2_P1.3mm_Open_Pad1.0x1.5mm
LOGO1: Logo_Open_Hardware_Small; CC-BY-ND-SA
Module1: CC1101
Module2: HB_Pro_Mini_ATMEGA1284P_FUEL4EP
Q1: IRLU024N; TO-251-3_Vertical
R1: 470; R_Axial_DIN0207_L6.3mm_D2.5mm_P2.54mm_Vertical
R3: 100K; R_Axial_DIN0207_L6.3mm_D2.5mm_P2.54mm_Vertical
R4, R5: 10K; R_Axial_DIN0207_L6.3mm_D2.5mm_P2.54mm_Vertical
SW1: config button; SW_PUSH_6mm_H5mm

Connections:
/A0: J1.1, JP5.1 (A), Module2.8A (PA0/A0)
/A1: J2.1, Module2.7A (PA1/A1)
/A2: J3.1, Module2.6A (PB3/A2)
/A3: J4.1, Module2.5A (PB2/A3)
/CONFIG: Module2.11C (PC6/TOSC), SW1.1
/D2: Module1.7C (GD0), Module2.5C (PD2)
/MISO: J5.5, Module1.5C (MISO), Module2.10A (PB6/MISO)
/MOSI: J5.3, Module1.3C (MOSI), Module2.11A (PB5/MOSI)
/RSET: J5.6, Module2.3A (RSTB)
/SCK: J5.4, Module1.4C (SCLK), Module2.9A (PB7/SCK)
/SCL: J6.3, J7.3, J8.3, J9.3, Module2.1E (PC0/SCL), R4.2
/SDA: J6.4, J7.4, J8.4, J9.4, Module2.2E (PC1/SDA), R5.2
/SS: Module1.8C (~CSN), Module2.12A (PB4/~SS)
/V_ACCU: JP3.2 (B), Module2.1A (V_ACCU)
/conBAT: BT1.2 (-), BT2.1 (+), JP4.1 (A)
/minusBAT: BT2.2 (-), J5.2, J10.3, JP1.1 (A), JP4.2 (B), Q1.2 (D)
/plusBAT: BT1.1 (+), J10.2, JP2.1 (A), JP3.1 (A), JP5.2 (B)
GND: C1.2, D1.1 (K), J1.2, J2.2, J3.2, J4.2, J6.2, J7.2, J8.2, J9.2, JP1.2 (B), Module1.1A (GND), Module1.2C (GND), Module1.3A (GND), Module2.2A (GND), Module2.4C (GND), Q1.3 (S), SW1.2
unnamed: D1.2 (A), R1.1
unnamed: Module2.7C (PD4), R1.2
unnamed: Q1.1 (G), R3.2
VCC: C1.1, J5.1, J6.1, J7.1, J8.1, J9.1, J10.1, JP2.2 (B), Module1.1C (VCC), Module2.4A (VCC), R3.1, R4.1, R5.1

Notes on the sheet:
caution!
caution! do not connect if JP5 is bridged
caution! do not solder both JP2 and JP3
2x Keystone 2460 battery holders
do not insert a BT2 battery if JP4 is soldered
connect an 8.6 cm long isolated wire as antenna
alternatively, an Arduino Pro Mini or a Tindie Pro Mini XL V2 can be used, too. Please do not forget to set JP2, JP3, JP4, and JP5 appropriately!

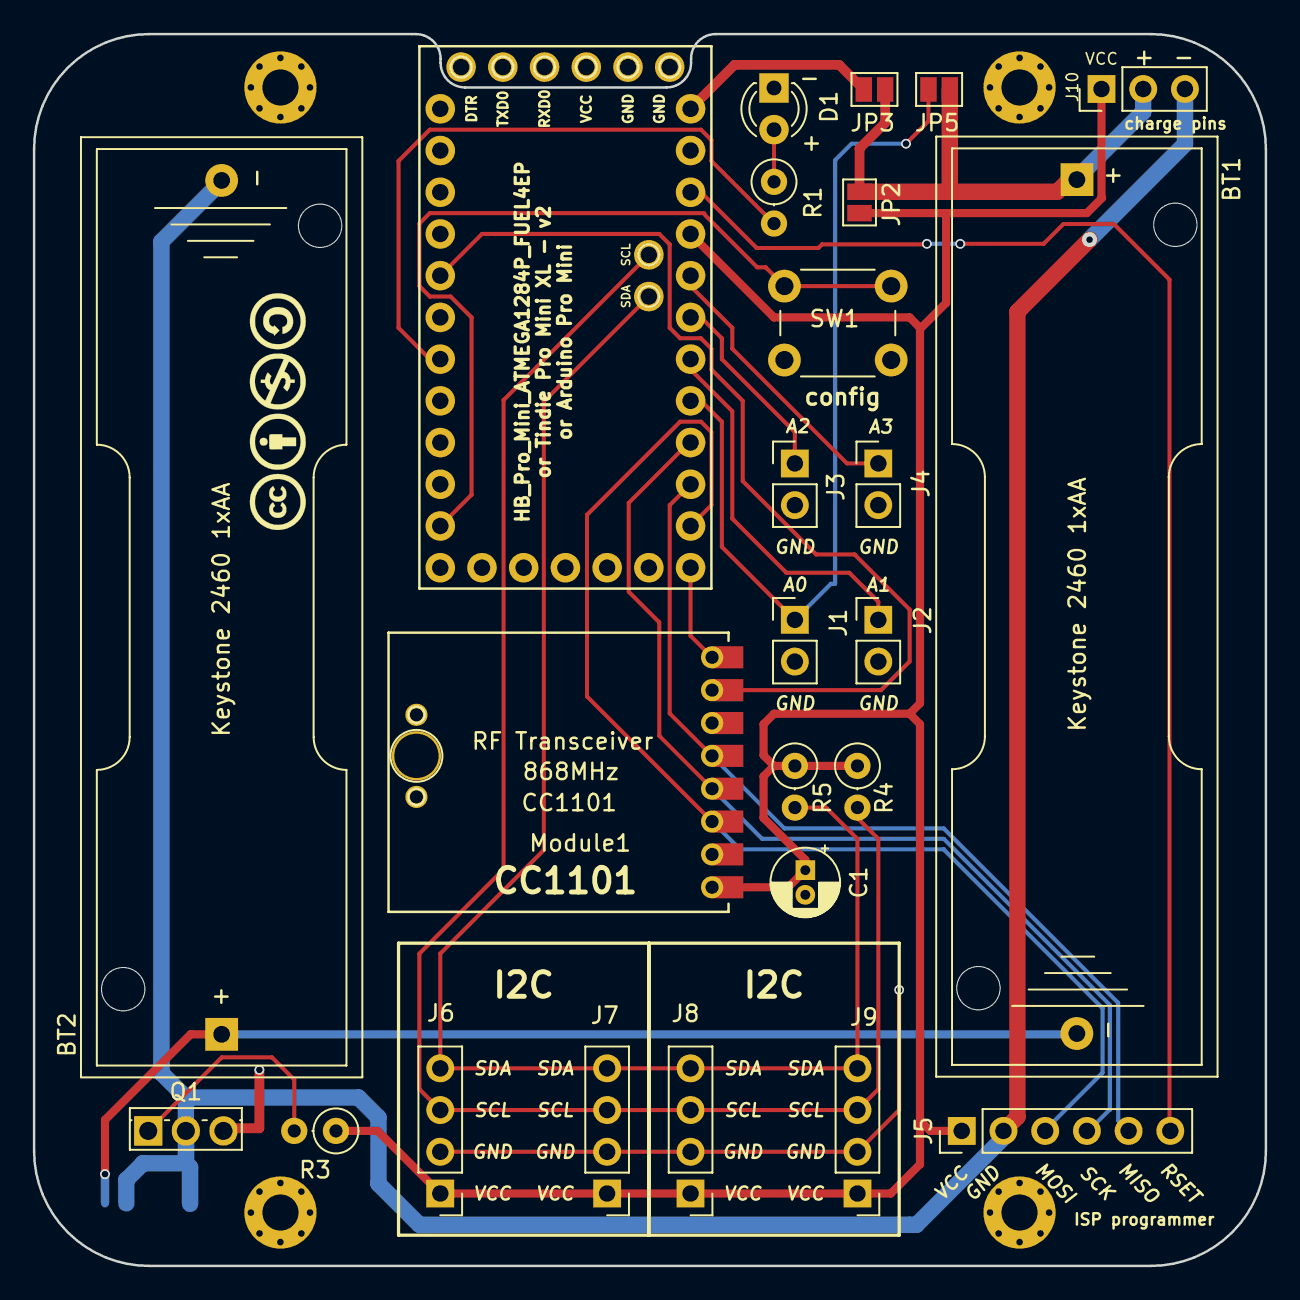
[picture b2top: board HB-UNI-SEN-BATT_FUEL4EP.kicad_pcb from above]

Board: 2 copper layers, 75.0 x 75.0 mm, 32 parts (0 on the bottom side), 22 nets.

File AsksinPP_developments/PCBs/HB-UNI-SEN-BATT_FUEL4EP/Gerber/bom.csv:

Designator,Footprint,Quantity,Value,LCSC Part #
"BT1, BT2",BatteryHolder_Keystone_2460_1xAA,2,AA,
C1,CP_Radial_D4.0mm_P1.50mm,1,10uF,
D1,LED_D3.0mm,1,LED red 3mm,
"H1, H2, H3, H4",MountingHole_2.2mm_M2_Pad_Via,4,MountingHole,
"J1, J2, J3, J4",PinHeader_1x02_P2.54mm_Vertical,4,Conn_01x02,
J10,PinHeader_1x03_P2.54mm_Vertical,1,charge,
J5,PinHeader_1x06_P2.54mm_Vertical,1,ISP Programmer,
"J6, J7, J8, J9",PinHeader_1x04_P2.54mm_Vertical,4,Conn_01x04,
JP1,SolderJumper-2_P1.3mm_Open_Pad1.0x1.5mm,1,NO,
JP2,SolderJumper-2_P1.3mm_Bridged_Pad1.0x1.5mm,1,cut for accus,
LOGO1,CC-BY-ND-SA,1,Logo_Open_Hardware_Small,
Module1,CC1101,1,CC1101,
Module2,Tindie_ArduinoProMiniXL_1284P_V2,1,Tindie_Pro_Mini_XL_V2,
Q1,TO-251-3_Vertical,1,IRLU024N,
R1,R_Axial_DIN0207_L6.3mm_D2.5mm_P2.54mm_Vertical,1,470,
R3,R_Axial_DIN0207_L6.3mm_D2.5mm_P2.54mm_Vertical,1,100K,
"R4, R5",R_Axial_DIN0207_L6.3mm_D2.5mm_P2.54mm_Vertical,2,10K,
SW1,SW_PUSH_6mm_H5mm,1,config button,

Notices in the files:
AsksinPP_developments/PCBs/HB-UNI-SEN-BATT_ATMega1284P_E07-868MS10_FUEL4EP/HB-UNI-SEN-BATT_ATMega1284P_E07-868MS10_FUEL4EP.kicad_sch:
Creative Commons License, non-commercial
AsksinPP_developments/PCBs/HB-UNI-SEN-BATT_ATMega1284P_E07-868MS10_FUEL4EP/README.md:
License: CC BY-NC-SA 4.0
AsksinPP_developments/PCBs/HB_Pro_Mini_ATMEGA1284P_FUEL4EP/HB_Pro_Mini_ATMEGA1284P_FUEL4EP.kicad_sch:
https://creativecommons.org/licenses/by-nc-sa/4.0
This work is licensed under CC BY-NC-SA 4.0
